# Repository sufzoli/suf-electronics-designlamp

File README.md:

# suf-electronics-designlamp
Hardware and software for modifying my floor standing design lamp

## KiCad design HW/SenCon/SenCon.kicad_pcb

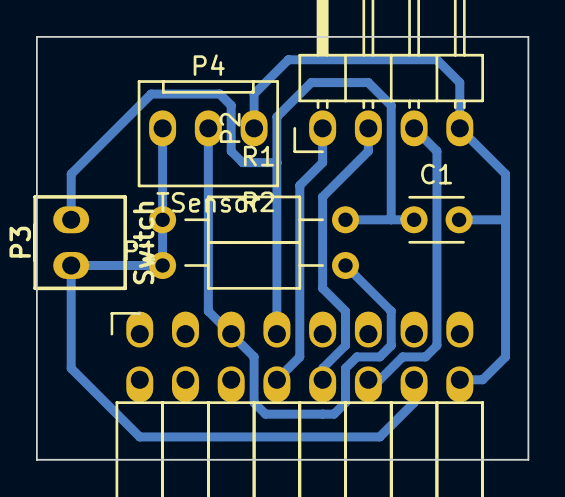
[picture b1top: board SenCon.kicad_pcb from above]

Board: 2 copper layers, 27.3 x 23.5 mm, 7 parts (0 on the bottom side), 7 nets.

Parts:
C1: 1nF; C_Disc_D3_P2.5
P1: BUS; Socket_Strip_Angled_2x08
P2: Control; Pin_Header_Angled_1x04
P3: Switch; CONN_NCW254-02S
P4: TSensor; CONN_NCW254-03S
R1, R2: 3,3K; Resistor_Horizontal_RM10mm

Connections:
/GPIO4: P1.5, P4.2, R2.2
/GPIO5: C1.1, P1.7, P3.2, R1.2
/GPIO12: P1.10, P2.2
/GPIO13: P1.12, P2.3
/GPIO14: P1.8, P2.1
GND: C1.2, P1.16, P2.4, P4.3
VCC: P1.14, P3.1, P4.1, R1.1, R2.1

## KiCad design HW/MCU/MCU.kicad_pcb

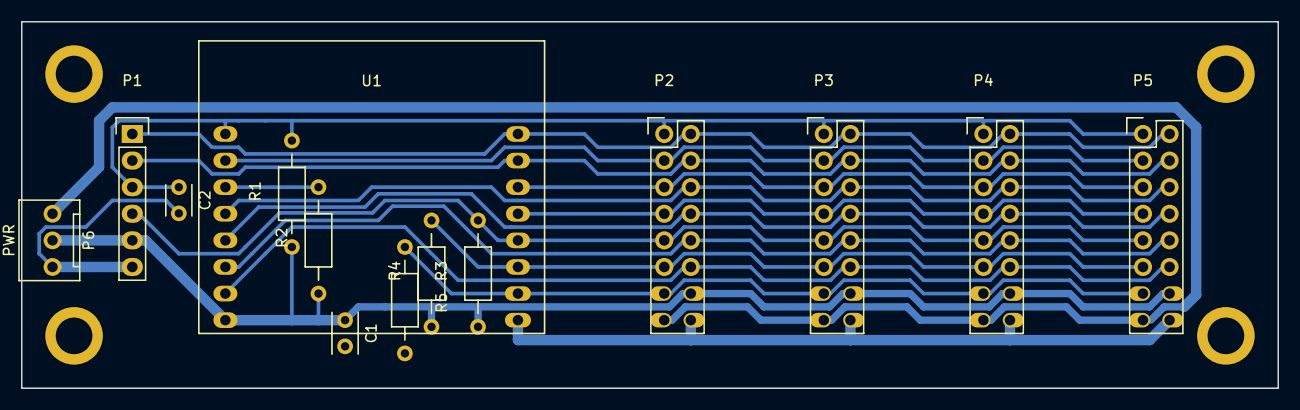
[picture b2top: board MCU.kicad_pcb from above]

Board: 2 copper layers, 120.0 x 35.0 mm, 18 parts (0 on the bottom side), 17 nets.

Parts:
C1: 1uF/10V; C_Rect_L4_W2.5_P2.5
C2: 470pF; C_Disc_D3_P2.5
MNT_HOLE_3.5, MNT_HOLE_3.5#2, MNT_HOLE_3.5#3, MNT_HOLE_3.5#4: Val**; MNT_HOLE_3.5
P1: ISP; Pin_Header_Straight_1x06
P2, P3, P4, P5: BUS; Pin_Header_Straight_2x08
P6: PWR; CONN_NCW254-03S
R1, R2, R3, R4, R5: 12K; Resistor_Horizontal_RM10mm
U1: ESP_BreakOut; ESP_Breakout

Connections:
/ADC: P2.3, P3.3, P4.3, P5.3, U1.2
/GPIO0: P1.4, P2.9, P3.9, P4.9, P5.9, R3.2, U1.12
/GPIO2: P2.11, P3.11, P4.11, P5.11, R4.2, U1.11
/GPIO4: P2.5, P3.5, P4.5, P5.5, U1.14
/GPIO5: P2.7, P3.7, P4.7, P5.7, U1.13
/GPIO12: P2.10, P3.10, P4.10, P5.10, U1.6
/GPIO13: P2.12, P3.12, P4.12, P5.12, U1.7
/GPIO14: P2.8, P3.8, P4.8, P5.8, U1.5
/GPIO15: P2.13, P3.13, P4.13, P5.13, R5.1, U1.10
/GPIO16: P2.6, P3.6, P4.6, P5.6, U1.4
/RESET: C2.1, P1.3, P2.1, P3.1, P4.1, P5.1, R1.2, U1.1
/RXD: P1.2, P2.4, P3.4, P4.4, P5.4, U1.15
/TXD: P1.1, P2.2, P3.2, P4.2, P5.2, U1.16
GND: C1.2, C2.2, P1.6, P2.16, P3.16, P4.16, P5.16, P6.3, R5.2, U1.9
unnamed: R2.2, U1.3
VCC: C1.1, P1.5, P2.14, P3.14, P4.14, P5.14, P6.2, R1.1, R2.1, R3.1, R4.1, U1.8
VDD: P2.15, P3.15, P4.15, P5.15, P6.1

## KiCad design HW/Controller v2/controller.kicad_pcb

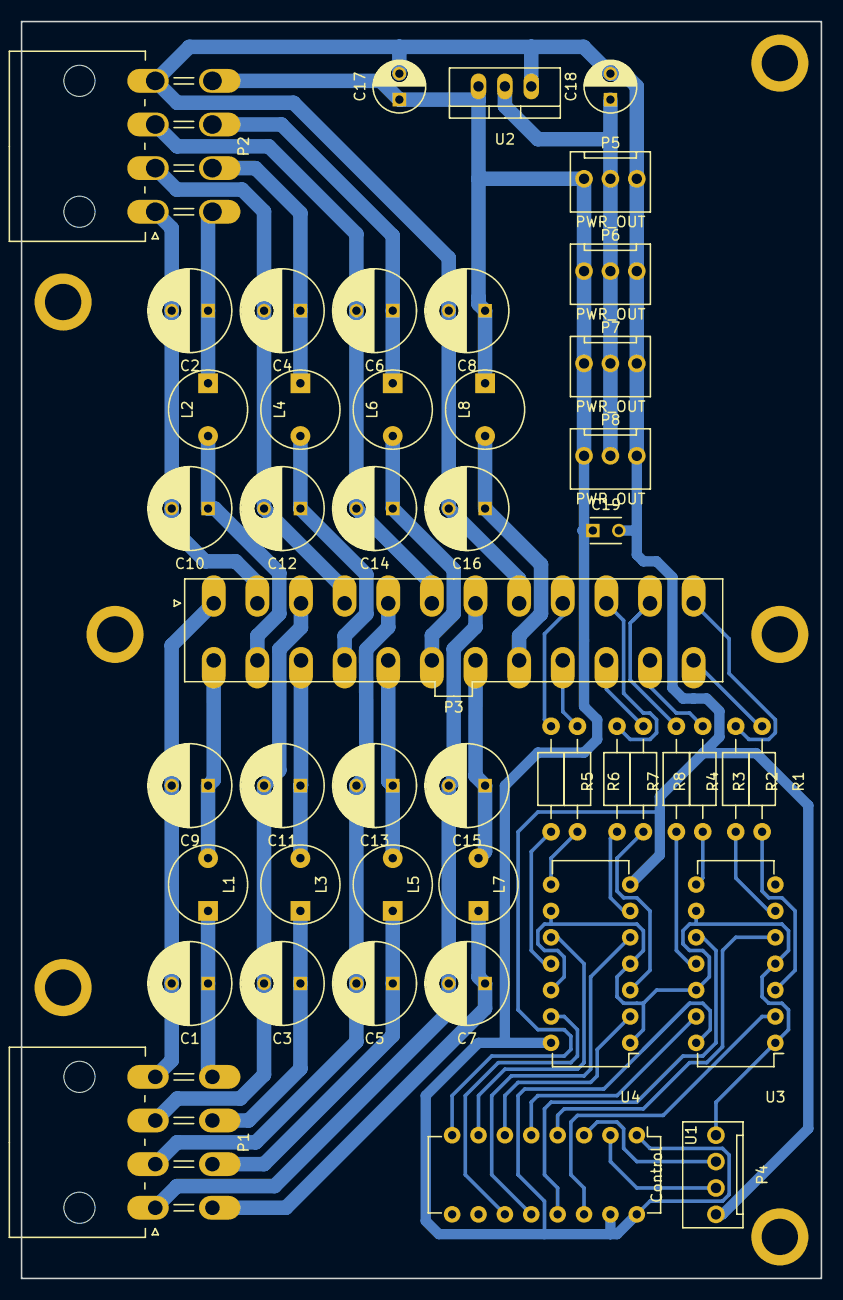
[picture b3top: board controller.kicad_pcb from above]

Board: 2 copper layers, 77.0 x 121.0 mm, 53 parts (0 on the bottom side), 52 nets.

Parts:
C1, C2, C3, C4, C5, C6, C7, C8, C9, C10, C11, C12, C13, C14, C15, C16: 1000uF/10V; C_Radial_D8_L11.5_P3.5
C17: 100uF/10V; C_Radial_D5_L6_P2.5
C18: 22uF/6,3V; C_Radial_D5_L6_P2.5
C19: 1uF/10V; C_Disc_D3_P2.5
L1, L2, L3, L4, L5, L6, L7, L8: 1,5uH/5,4A; INDUCTOR_V
MNT_HOLE_3.5, MNT_HOLE_3.5#2, MNT_HOLE_3.5#3, MNT_HOLE_3.5#4, MNT_HOLE_3.5#5, MNT_HOLE_3.5#6: Val**; MNT_HOLE_3.5
P1: PWR1; Molex_MiniFit-JR-5569-08A2_2x04x4.20mm_Angled
P2: PWR2; Molex_MiniFit-JR-5569-08A2_2x04x4.20mm_Angled
P3: Light; Molex_MiniFit-JR-5556-24A_2x12x4.20mm_Straight
P4: Control; CONN_NCW254-04S
P5, P6, P7, P8: PWR_OUT; CONN_NCW254-03S
R1, R2, R3, R4, R5, R6, R7, R8: 470; Resistor_Horizontal_RM10mm
U1: 4094; DIP-16_W7.62mm
U2: LD1117V33; TO-220_Neutral123_Vertical
U3, U4: 74HCT08; DIP-14_W7.62mm

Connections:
GND: C8.2, C16.2, C17.2, C18.2, C19.2, P2.4, P3.8, P4.4, P5.3, P6.3, P7.3, P8.3, U1.8, U2.1, U3.7, U4.7
unnamed: C1.1, L1.1, P1.8
unnamed: C1.2, C9.2, P1.4, P3.1
unnamed: C2.1, L2.1, P2.5
unnamed: C3.1, L3.1, P1.7
unnamed: C4.1, L4.1, P2.6
unnamed: C5.1, L5.1, P1.6
unnamed: C6.1, L6.1, P2.7
unnamed: C7.1, L7.1, P1.5
unnamed: C9.1, L1.2, P3.13
unnamed: C10.1, L2.2, P3.14
unnamed: C2.2, C10.2, P2.1, P3.2
unnamed: C11.1, L3.2, P3.15
unnamed: C3.2, C11.2, P1.3, P3.3
unnamed: C12.1, L4.2, P3.16
unnamed: C4.2, C12.2, P2.2, P3.4
unnamed: C13.1, L5.2, P3.17
unnamed: C5.2, C13.2, P1.2, P3.5
unnamed: C14.1, L6.2, P3.18
unnamed: C6.2, C14.2, P2.3, P3.6
unnamed: C15.1, L7.2, P3.19
unnamed: C7.2, C15.2, P1.1, P3.7
unnamed: C16.1, L8.2, P3.20
unnamed: P3.9, R5.1
unnamed: P3.10, R7.1
unnamed: P3.11, R4.1
unnamed: P3.12, R2.1
unnamed: P3.21, R6.1
unnamed: P3.22, R8.1
unnamed: P3.23, R3.1
unnamed: P3.24, R1.1
unnamed: P4.1, U3.1, U3.4, U3.9, U3.12, U4.1, U4.4, U4.9, U4.12
unnamed: P4.2, U1.3
unnamed: P4.3, U1.2
unnamed: R1.2, U3.3
unnamed: R2.2, U3.6
unnamed: R3.2, U3.8
unnamed: R4.2, U3.11
unnamed: R5.2, U4.11
unnamed: R6.2, U4.8
unnamed: R7.2, U4.6
unnamed: R8.2, U4.3
unnamed: U1.4, U3.5
unnamed: U1.5, U3.13
unnamed: U1.6, U4.2
unnamed: U1.7, U4.10
unnamed: U1.11, U4.13
unnamed: U1.12, U4.5
unnamed: U1.13, U3.10
unnamed: U1.14, U3.2
VCC: C18.1, P5.2, P6.2, P7.2, P8.2, U2.2
VDD: C8.1, C17.1, C19.1, L8.1, P2.8, P5.1, P6.1, P7.1, P8.1, U1.1, U1.15, U1.16, U2.3, U3.14, U4.14

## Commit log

2016-12-07 Software first version
2016-12-12 Switch handling, Frame timer (unfinished)
2016-12-19 Temperature sensor and switch controll added
2016-12-20 Version check addaed (/api/ver), OTA tested
2016-12-22 Feature: Cooling Sparking control Bug: DS18B20 read timing Feature: AJAX read setting at control page load
2017-01-14 ArrayList class added
2021-03-20 Unknown changes
